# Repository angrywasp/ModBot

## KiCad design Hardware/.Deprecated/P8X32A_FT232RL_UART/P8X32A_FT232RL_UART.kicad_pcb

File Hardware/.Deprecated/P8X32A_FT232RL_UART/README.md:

Not intended for new designs. Outputs are unbuffered. Suitable only for projects that will use USB power through this module

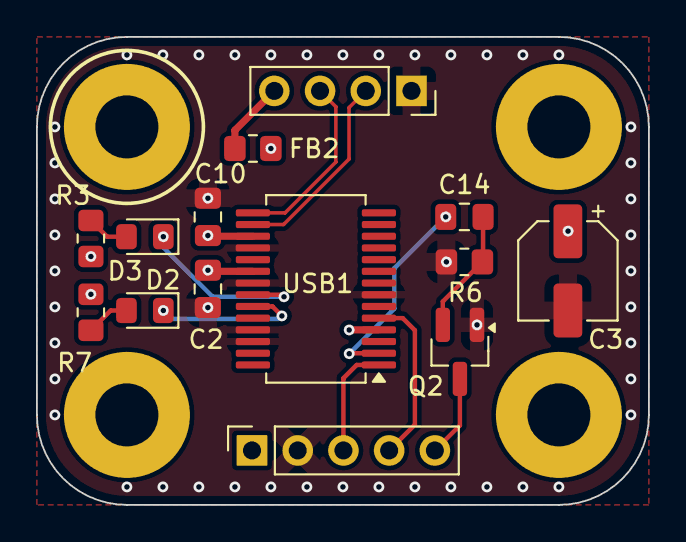
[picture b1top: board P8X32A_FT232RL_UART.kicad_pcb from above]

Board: 4 copper layers, 34.0 x 26.0 mm, 14 parts (0 on the bottom side), 15 nets.

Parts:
C2, C10, C14: 0.1uF; C_0805_2012Metric_Pad1.18x1.45mm_HandSolder
C3: 47uF; CP_Elec_5x5.3
D2: BLUE; LED_0805_2012Metric_Pad1.15x1.40mm_HandSolder
D3: RED; LED_0805_2012Metric_Pad1.15x1.40mm_HandSolder
FB2: 220; R_0805_2012Metric_Pad1.20x1.40mm_HandSolder
J1: Conn_01x05; PinSocket_1x05_P2.54mm_Vertical
J2: Conn_01x04; PinSocket_1x04_P2.54mm_Vertical
Q2: NPN; SOT-23_Handsoldering
R3, R7: 330; R_0805_2012Metric_Pad1.20x1.40mm_HandSolder
R6: 10k; R_0805_2012Metric_Pad1.20x1.40mm_HandSolder
USB1: FT232L; SSOP-28_5.3x10.2mm_P0.65mm

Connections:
+3.3V: C10.2, USB1.4 (VCCIO), USB1.17 (3V3OUT)
+5V: C2.2, C3.1, FB2.2, J1.1, R3.1, R7.2, USB1.20 (VCC)
DTR: C14.1, USB1.2 (DTR)
GND: C2.1, C3.2, C10.1, J1.2, J2.1, Q2.1 (E), R6.2, USB1.7 (GND), USB1.18 (GND), USB1.21 (GND), USB1.25 (AGND), USB1.26 (TEST)
unnamed: D2.2 (A), R7.1
unnamed: D2.1 (K), USB1.23 (CBUS0)
unnamed: D3.2 (A), R3.2
unnamed: D3.1 (K), USB1.22 (CBUS1)
unnamed: FB2.1, J2.4
unnamed: C14.2, Q2.2 (B), R6.1
RESn: J1.5, Q2.3 (C)
RXD: J1.4, USB1.5 (RXD)
TXD: J1.3, USB1.1 (TXD)
USB+: J2.3, USB1.15 (USBD+)
USB-: J2.2, USB1.16 (USBD-)

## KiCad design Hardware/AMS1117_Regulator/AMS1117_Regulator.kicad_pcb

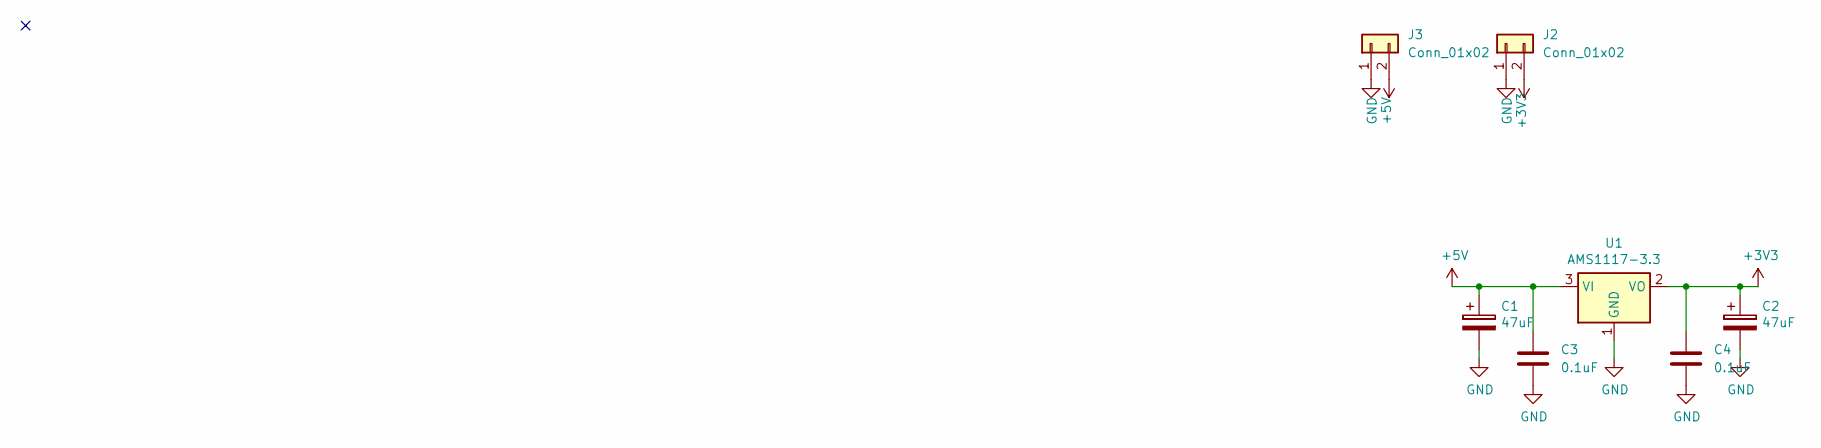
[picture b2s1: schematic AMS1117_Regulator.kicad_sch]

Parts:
C1, C2: 47uF; CP_Elec_5x5.3
C3, C4: 0.1uF; C_0805_2012Metric_Pad1.18x1.45mm_HandSolder
J2, J3: Conn_01x02; PinSocket_1x02_P2.54mm_Vertical
U1: AMS1117-3.3; SOT-223-3_TabPin2

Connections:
+3V3: C2.1, C4.1, J2.2, U1.2 (VO)
+5V: C1.1, C3.1, J3.2, U1.3 (VI)
GND: C1.2, C2.2, C3.2, C4.2, J2.1, J3.1, U1.1 (GND)

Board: 2 copper layers, 7 parts (0 on the bottom side), 3 nets, no tracks yet.

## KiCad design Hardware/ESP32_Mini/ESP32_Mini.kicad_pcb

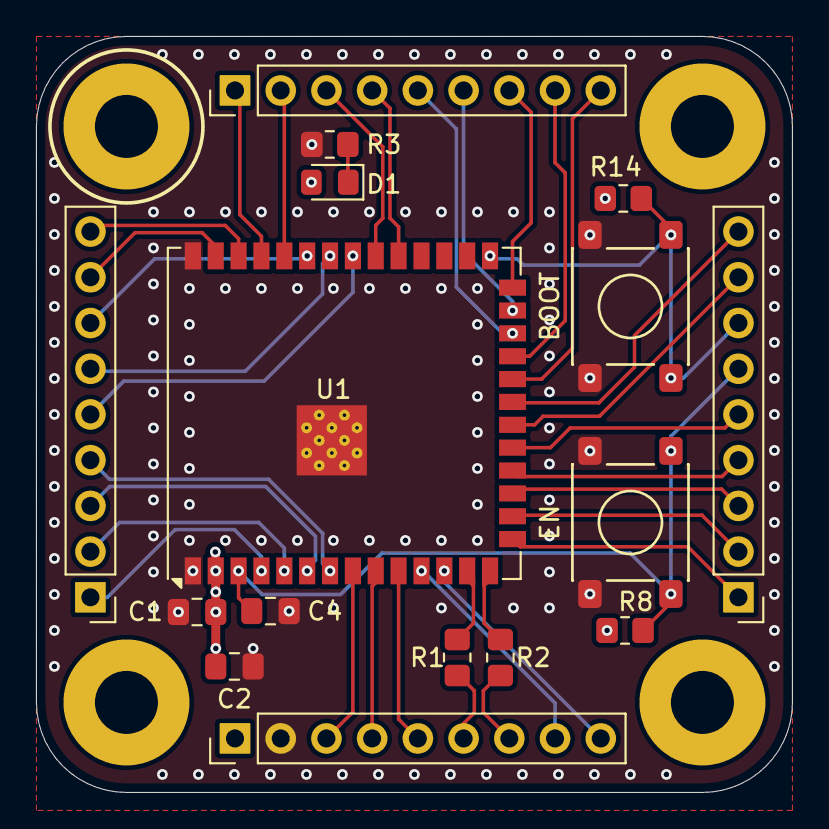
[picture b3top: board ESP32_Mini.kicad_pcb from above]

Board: 4 copper layers, 42.0 x 42.0 mm, 16 parts (0 on the bottom side), 39 nets.

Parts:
C1, C4: 0.1uF; C_0805_2012Metric_Pad1.18x1.45mm_HandSolder
C2: 10uF; C_0805_2012Metric_Pad1.18x1.45mm_HandSolder
D1: LED; LED_0805_2012Metric_Pad1.15x1.40mm_HandSolder
J1, J2: Conn_01x09; PinHeader_1x09_P2.54mm_Vertical
J3, J4: Conn_01x08; PinHeader_1x09_P2.54mm_Vertical
R1, R2: 22; R_0805_2012Metric_Pad1.20x1.40mm_HandSolder
R3, R8, R14: 10k; R_0805_2012Metric_Pad1.20x1.40mm_HandSolder
SW2: BOOT; SW_SPST
SW9: EN; SW_SPST
U1: ESP32-S3-WROOM-1; ESP32-S3-WROOM-1U

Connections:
+3.3V: C1.1, C2.1, D1.2 (A), J3.1, R8.2, R14.2, U1.2 (3V3)
/USB_D+: R2.2, U1.14 (USB_D+)
/USB_D-: R1.2, U1.13 (USB_D-)
D+: J3.7, R2.1
D-: J3.6, R1.1
EN: C4.1, J4.6, R8.1, SW9.2, U1.3 (EN)
GND: C1.2, C2.2, C4.2, J3.2, R3.1, SW2.1, SW9.1, U1.1 (GND), U1.40 (GND), U1.41 (GND)
IO0: J4.7, R14.1, SW2.2, U1.27 (IO0)
IO1: J1.8, U1.39 (IO1)
IO2: J1.9, U1.38 (IO2)
IO3: J4.1, U1.15 (IO3)
IO4: J1.1, U1.4 (IO4)
IO5: J1.2, U1.5 (IO5)
IO6: J1.3, U1.6 (IO6)
IO7: J1.4, U1.7 (IO7)
IO8: J3.9, U1.12 (IO8)
IO9: J4.3, U1.17 (IO9)
IO10: J4.4, U1.18 (IO10)
IO11: J4.5, U1.19 (IO11)
IO12: J4.8, U1.20 (IO12)
IO13: J4.9, U1.21 (IO13)
IO14: J2.9, U1.22 (IO14)
IO15: J3.3, U1.8 (IO15)
IO16: J3.4, U1.9 (IO16)
IO17: J3.5, U1.10 (IO17)
IO18: J3.8, U1.11 (IO18)
IO21: J2.8, U1.23 (IO21)
IO38: J2.4, U1.31 (IO38)
IO39: J2.3, U1.32 (IO39)
IO40: J1.5, U1.33 (IO40)
IO41: J1.6, U1.34 (IO41)
IO42: J1.7, U1.35 (IO42)
IO45: J2.7, U1.26 (IO45)
IO46: J4.2, U1.16 (IO46)
IO47: J2.5, U1.24 (IO47)
IO48: J2.6, U1.25 (IO48)
unnamed: D1.1 (K), R3.2
RXD0: J2.2, U1.36 (RXD0)
TXD0: J2.1, U1.37 (TXD0)

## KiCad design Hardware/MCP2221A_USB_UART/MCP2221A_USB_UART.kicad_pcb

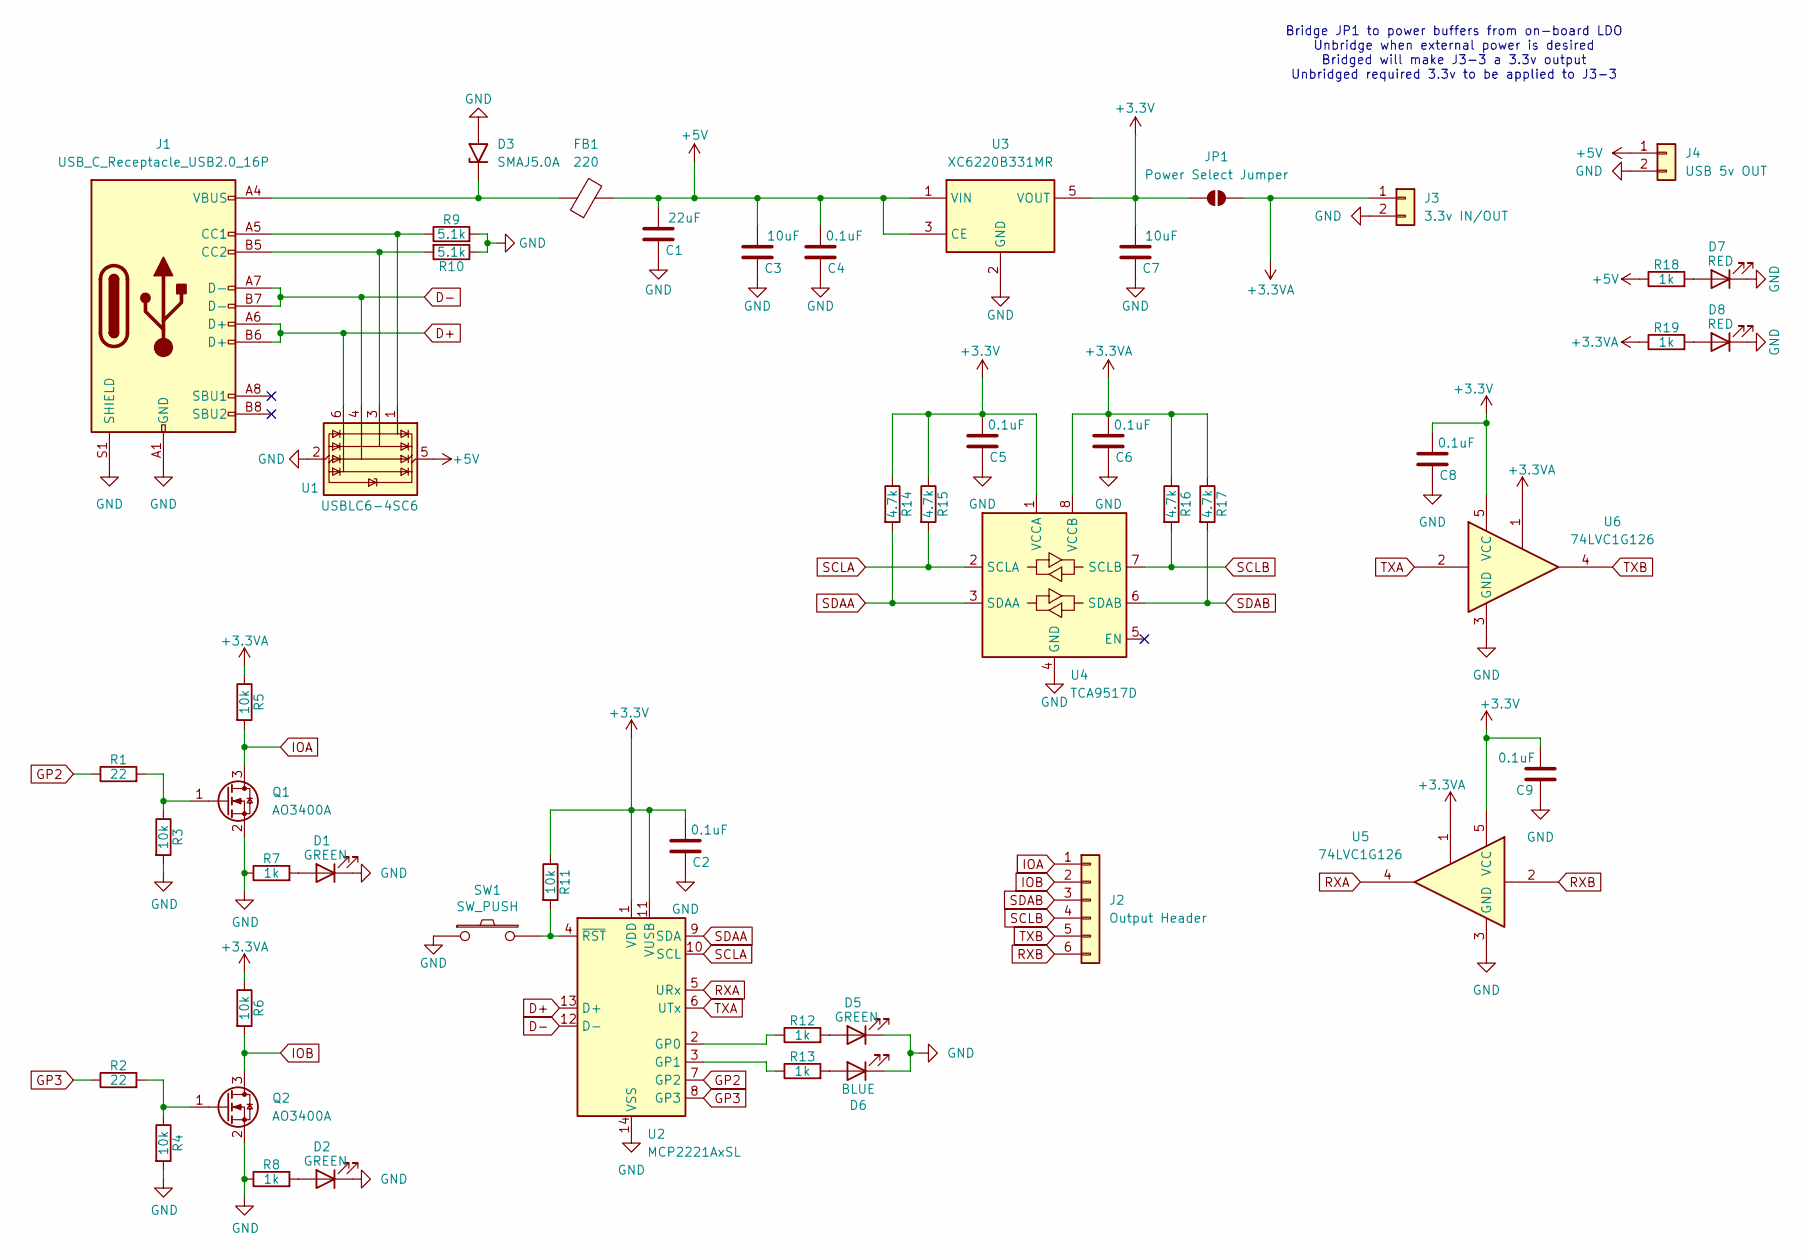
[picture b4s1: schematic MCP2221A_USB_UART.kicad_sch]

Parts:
C1: 22uF; C_0805_2012Metric_Pad1.18x1.45mm_HandSolder
C2, C4, C5, C6, C8, C9: 0.1uF; C_0805_2012Metric_Pad1.18x1.45mm_HandSolder
C3, C7: 10uF; C_0805_2012Metric_Pad1.18x1.45mm_HandSolder
D1, D2, D5: GREEN; LED_0805_2012Metric_Pad1.15x1.40mm_HandSolder
D3: SMAJ5.0A; D_SMA
D6: BLUE; LED_0805_2012Metric_Pad1.15x1.40mm_HandSolder
D7, D8: RED; LED_0805_2012Metric_Pad1.15x1.40mm_HandSolder
FB1: 220; R_0805_2012Metric_Pad1.20x1.40mm_HandSolder
J1: USB_C_Receptacle_USB2.0_16P; USB_C_Receptacle_HCTL_HC-TYPE-C-16P-01A
J2: Output Header; PinHeader_1x06_P2.54mm_Vertical
J3: 3.3v IN/OUT; PinHeader_1x02_P2.54mm_Vertical
J4: USB 5v OUT; PinHeader_1x02_P2.54mm_Vertical
JP1: Power Select Jumper; SolderJumper-2_P1.3mm_Open_RoundedPad1.0x1.5mm
Q1, Q2: AO3400A; SOT-23
R1, R2: 22; R_0805_2012Metric_Pad1.20x1.40mm_HandSolder
R3, R4, R5, R6, R11: 10k; R_0805_2012Metric_Pad1.20x1.40mm_HandSolder
R7, R8, R12, R13, R18, R19: 1k; R_0805_2012Metric_Pad1.20x1.40mm_HandSolder
R9, R10: 5.1k; R_0805_2012Metric_Pad1.20x1.40mm_HandSolder
R14, R15, R16, R17: 4.7k; R_0805_2012Metric_Pad1.20x1.40mm_HandSolder
SW1: SW_PUSH; SW_SPST
U1: USBLC6-4SC6; SOT-23-6
U2: MCP2221AxSL; SOIC-14_3.9x8.7mm_P1.27mm
U3: XC6220B331MR; SOT-23-5
U4: TCA9517D; SOIC-8_3.9x4.9mm_P1.27mm
U5, U6: 74LVC1G126; SOT-23-5

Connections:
+3.3V: C2.2, C5.2, C7.2, C8.2, C9.2, JP1.2 (B), R11.1, R14.1, R15.1, U2.1 (VDD), U2.11 (VUSB), U3.5 (VOUT), U4.1 (VCCA), U5.5 (VCC), U6.5 (VCC)
+3.3VA: C6.2, J3.1, JP1.1 (A), R5.1, R6.1, R16.1, R17.1, R19.1, U4.8 (VCCB), U5.1, U6.1
+5V: C1.2, C3.2, C4.2, FB1.2, J4.1, R18.1, U1.5 (VBUS), U3.1 (VIN), U3.3 (CE)
D+: J1.A6 (D+), J1.B6 (D+), U1.6 (I/O4), U2.13 (D+)
D-: J1.A7 (D-), J1.B7 (D-), U1.4 (I/O3), U2.12 (D-)
GND: C1.1, C2.1, C3.1, C4.1, C5.1, C6.1, C7.1, C8.1, C9.1, D1.1 (K), D2.1 (K), D3.2 (A2), D5.1 (K), D6.1 (K), D7.1 (K), D8.1 (K), J1.A1 (GND), J1.A12 (GND), J1.B1 (GND), J1.B12 (GND), J1.S1 (SHIELD), J3.2, J4.2, Q1.2 (S), Q2.2 (S), R3.2, R4.2, R7.1, R8.1, R9.2, R10.1, SW1.1, U1.2 (GND), U2.14 (VSS), U3.2 (GND), U4.4 (GND), U5.3 (GND), U6.3 (GND)
GP2: R1.1, U2.7 (GP2)
GP3: R2.1, U2.8 (GP3)
IOA: J2.1, Q1.3 (D), R5.2
IOB: J2.2, Q2.3 (D), R6.2
unnamed: D1.2 (A), R7.2
unnamed: D2.2 (A), R8.2
unnamed: D3.1 (A1), FB1.1, J1.A4 (VBUS), J1.A9 (VBUS), J1.B4 (VBUS), J1.B9 (VBUS)
unnamed: D5.2 (A), R12.2
unnamed: D6.2 (A), R13.2
unnamed: D7.2 (A), R18.2
unnamed: D8.2 (A), R19.2
unnamed: J1.A5 (CC1), R9.1, U1.1 (I/O1)
unnamed: J1.B5 (CC2), R10.2, U1.3 (I/O2)
unnamed: Q1.1 (G), R1.2, R3.1
unnamed: Q2.1 (G), R2.2, R4.1
unnamed: R12.1, U2.2 (GP0)
unnamed: R13.1, U2.3 (GP1)
unnamed: R11.2, SW1.2, U2.4 (~RST)
RXA: U2.5 (URx), U5.4
RXB: J2.6, U5.2
SCLA: R15.2, U2.10 (SCL), U4.2 (SCLA)
SCLB: J2.4, R16.2, U4.7 (SCLB)
SDAA: R14.2, U2.9 (SDA), U4.3 (SDAA)
SDAB: J2.3, R17.2, U4.6 (SDAB)
TXA: U2.6 (UTx), U6.2
TXB: J2.5, U6.4

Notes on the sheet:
Bridge JP1 to power buffers from on-board LDO Unbridge when external power is desired Bridged will make J3-3 a 3.3v output Unbridged required 3.3v to be applied to J3-3

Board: 4 copper layers, 50 parts (0 on the bottom side), 32 nets, no tracks yet.

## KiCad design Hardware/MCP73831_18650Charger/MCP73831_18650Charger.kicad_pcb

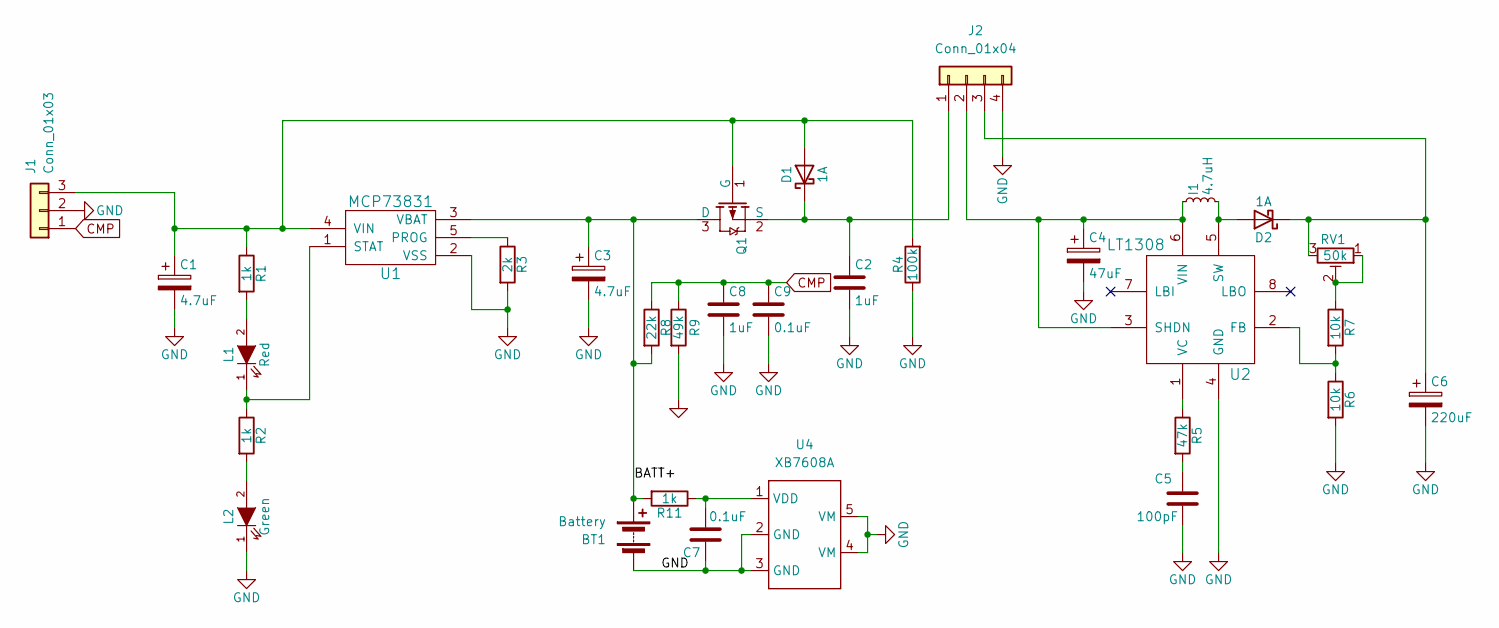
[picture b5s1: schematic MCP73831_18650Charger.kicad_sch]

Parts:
BT1: Battery; Keystone 18650
C1, C3: 4.7uF; CP_Elec_4x5.3
C2, C8: 1uF; C_0805_2012Metric_Pad1.18x1.45mm_HandSolder
C4: 47uF; CP_Elec_5x5.8
C5: 100pF; C_0805_2012Metric_Pad1.18x1.45mm_HandSolder
C6: 220uF; CP_Elec_6.3x7.7
C7, C9: 0.1uF; C_0805_2012Metric_Pad1.18x1.45mm_HandSolder
D1, D2: 1A; D_SMB_Handsoldering
I1: 4.7uH; L_APV_APH0630
J1: Conn_01x03; JST_XH_B3B-XH-A_1x03_P2.50mm_Vertical
J2: Conn_01x04; JST_XH_B4B-XH-A_1x04_P2.50mm_Vertical
L1: Red; LED_0805_2012Metric_Pad1.15x1.40mm_HandSolder
L2: Green; LED_0805_2012Metric_Pad1.15x1.40mm_HandSolder
Q1: PNP; SOT-23_Handsoldering
R1, R2, R11: 1k; R_0805_2012Metric_Pad1.20x1.40mm_HandSolder
R3: 2k; R_0805_2012Metric_Pad1.20x1.40mm_HandSolder
R4: 100k; R_0805_2012Metric_Pad1.20x1.40mm_HandSolder
R5: 47k; R_0805_2012Metric_Pad1.20x1.40mm_HandSolder
R6, R7: 10k; R_0805_2012Metric_Pad1.20x1.40mm_HandSolder
R8: 22k; R_0805_2012Metric_Pad1.20x1.40mm_HandSolder
R9: 49k; R_0805_2012Metric_Pad1.20x1.40mm_HandSolder
RV1: 50k; Potentiometer_Bourns_3224W_Vertical
U1: MCP73831; SOT-23-5_HandSoldering
U2: LT1308; SO-8_3.9x4.9mm_P1.27mm
U4: XB7608A; CPC-5

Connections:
/BATT+: BT1.1 (+), C3.1, Q1.3 (D), R8.2, R11.2, U1.3 (VBAT)
CMP: C8.1, C9.1, J1.1, R8.1, R9.1
GND: BT1.2 (-), C1.2, C2.2, C3.2, C4.2, C5.2, C6.2, C7.1, C8.2, C9.2, J1.2, J2.4, L2.1 (K), R3.2, R4.1, R6.2, R9.2, U1.2 (VSS), U2.4 (GND), U4.2 (GND), U4.3 (GND), U4.4 (VM), U4.5 (VM)
unnamed: C5.1, R5.2
unnamed: C1.1, D1.2 (A), J1.3, Q1.1 (G), R1.1, R4.2, U1.4 (VIN)
unnamed: C2.1, D1.1 (K), J2.1, Q1.2 (S)
unnamed: D2.2 (A), I1.2, U2.5 (SW)
unnamed: C6.1, D2.1 (K), J2.3, RV1.3
unnamed: C4.1, I1.1, J2.2, U2.3 (SHDN), U2.6 (VIN)
unnamed: L1.2 (A), R1.2
unnamed: L1.1 (K), R2.1, U1.1 (STAT)
unnamed: L2.2 (A), R2.2
unnamed: R7.1, RV1.1, RV1.2
unnamed: R3.1, U1.5 (PROG)
unnamed: R6.1, R7.2, U2.2 (FB)
unnamed: R5.1, U2.1 (VC)
unnamed: C7.2, R11.1, U4.1 (VDD)

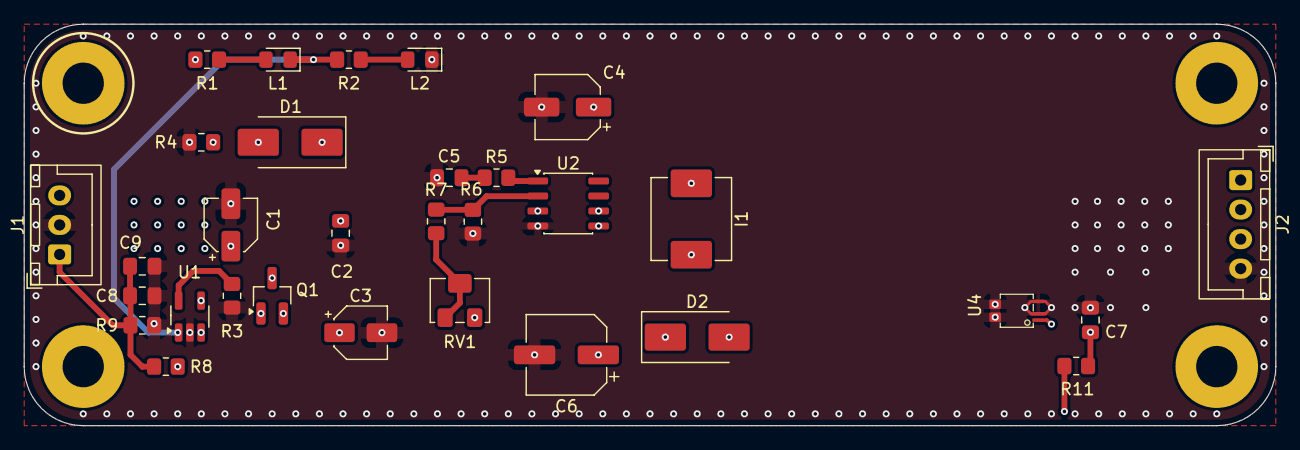
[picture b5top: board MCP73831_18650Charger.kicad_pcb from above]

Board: 4 copper layers, 106.0 x 34.0 mm, 32 parts (1 on the bottom side), 17 nets.

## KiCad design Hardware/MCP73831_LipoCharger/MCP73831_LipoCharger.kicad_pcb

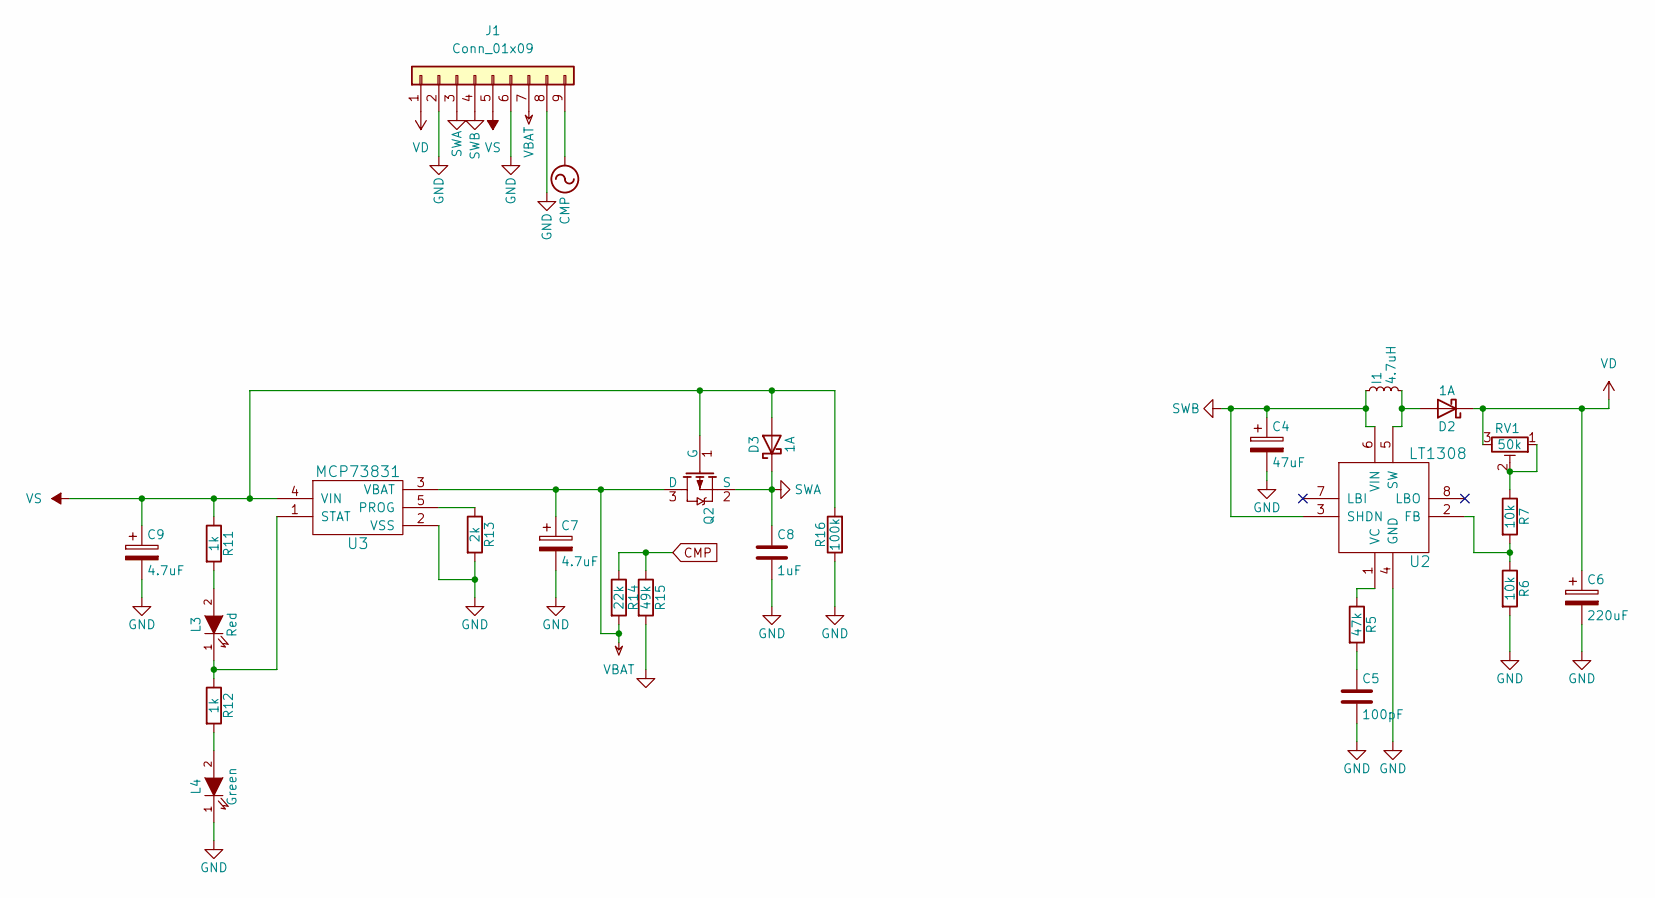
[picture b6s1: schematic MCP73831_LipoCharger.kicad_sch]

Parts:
C4: 47uF; CP_Elec_5x5.8
C5: 100pF; C_0805_2012Metric_Pad1.18x1.45mm_HandSolder
C6: 220uF; CP_Elec_6.3x7.7
C7, C9: 4.7uF; CP_Elec_4x5.3
C8: 1uF; C_0805_2012Metric_Pad1.18x1.45mm_HandSolder
D2, D3: 1A; D_SMB_Handsoldering
I1: 4.7uH; L_APV_APH0630
J1: Conn_01x09; PinSocket_1x09_P2.54mm_Vertical
L3: Red; LED_0805_2012Metric_Pad1.15x1.40mm_HandSolder
L4: Green; LED_0805_2012Metric_Pad1.15x1.40mm_HandSolder
Q2: P-Channel MOSFET; SOT-23_Handsoldering
R5: 47k; R_0805_2012Metric_Pad1.20x1.40mm_HandSolder
R6, R7: 10k; R_0805_2012Metric_Pad1.20x1.40mm_HandSolder
R11, R12: 1k; R_0805_2012Metric_Pad1.20x1.40mm_HandSolder
R13: 2k; R_0805_2012Metric_Pad1.20x1.40mm_HandSolder
R14: 22k; R_0805_2012Metric_Pad1.20x1.40mm_HandSolder
R15: 49k; R_0805_2012Metric_Pad1.20x1.40mm_HandSolder
R16: 100k; R_0805_2012Metric_Pad1.20x1.40mm_HandSolder
RV1: 50k; Potentiometer_Bourns_3224W_Vertical
U2: LT1308; SO-8_3.9x4.9mm_P1.27mm
U3: MCP73831; SOT-23-5_HandSoldering

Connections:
CMP: J1.9, R14.1, R15.1
GND: C4.2, C5.2, C6.2, C7.2, C8.2, C9.2, J1.2, J1.6, J1.8, L4.1 (K), R6.2, R13.2, R15.2, R16.1, U2.4 (GND), U3.2 (VSS)
unnamed: C5.1, R5.2
unnamed: D2.2 (A), I1.2, U2.5 (SW)
unnamed: L3.2 (A), R11.2
unnamed: L3.1 (K), R12.1, U3.1 (STAT)
unnamed: L4.2 (A), R12.2
unnamed: R7.1, RV1.1, RV1.2
unnamed: R6.1, R7.2, U2.2 (FB)
unnamed: R5.1, U2.1 (VC)
unnamed: R13.1, U3.5 (PROG)
SWA: C8.1, D3.1 (K), J1.3, Q2.2 (S)
SWB: C4.1, I1.1, J1.4, U2.3 (SHDN), U2.6 (VIN)
VBAT: C7.1, J1.7, Q2.3 (D), R14.2, U3.3 (VBAT)
VD: C6.1, D2.1 (K), J1.1, RV1.3
VS: C9.1, D3.2 (A), J1.5, Q2.1 (G), R11.1, R16.2, U3.4 (VIN)

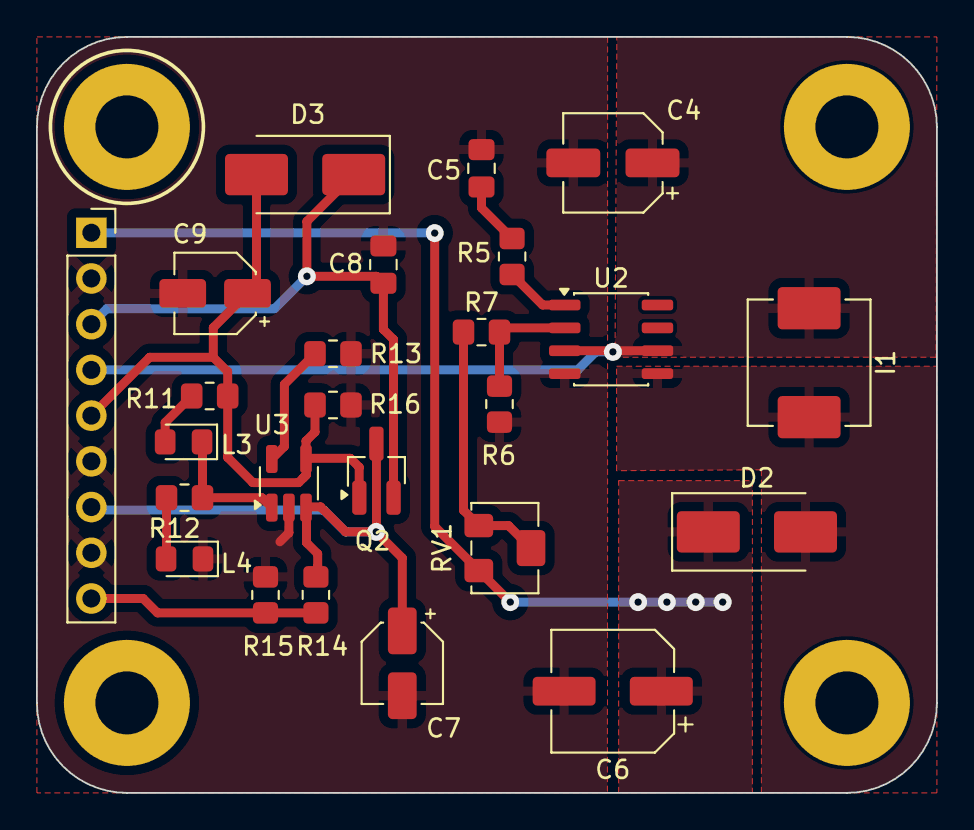
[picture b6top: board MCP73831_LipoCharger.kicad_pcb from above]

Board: 2 copper layers, 50.0 x 42.0 mm, 25 parts (0 on the bottom side), 16 nets.

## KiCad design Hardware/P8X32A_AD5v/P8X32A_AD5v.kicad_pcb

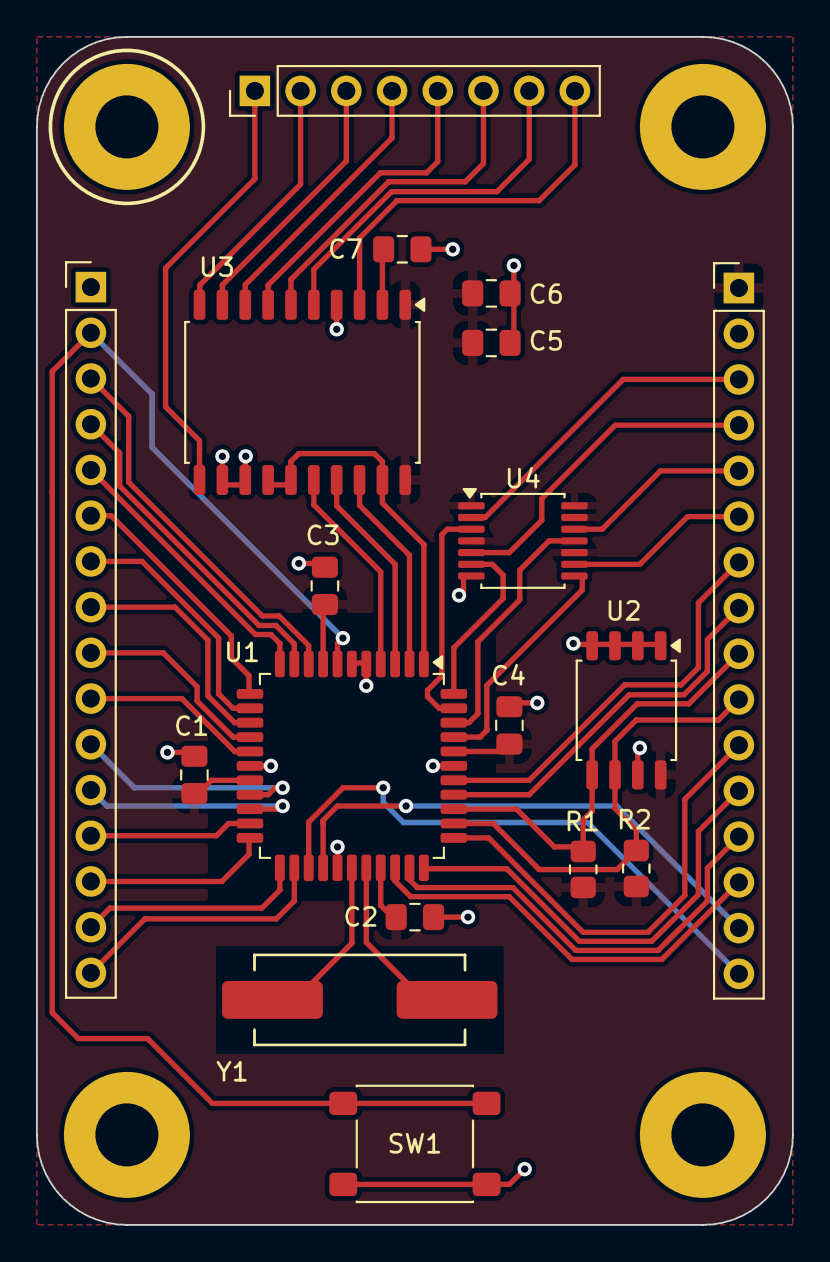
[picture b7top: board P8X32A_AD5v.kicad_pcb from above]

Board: 2 copper layers, 42.0 x 66.0 mm, 18 parts (0 on the bottom side), 50 nets.

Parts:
C1, C2, C3, C4, C6: 0.1uF; C_0805_2012Metric_Pad1.18x1.45mm_HandSolder
C5: 10uF; C_0805_2012Metric_Pad1.18x1.45mm_HandSolder
C7: 10nF; C_0805_2012Metric_Pad1.18x1.45mm_HandSolder
J1, J2: Conn_01x16; PinHeader_1x16_P2.54mm_Vertical
J3: Conn_01x08; PinHeader_1x08_P2.54mm_Vertical
R1, R2: 10k; R_0805_2012Metric_Pad1.20x1.40mm_HandSolder
SW1: SW_PUSH; SW_SPST_PTS645Sx43SMTR92
U1: Propeller; LQFP-44_10x10mm_P0.8mm
U2: 24LC512; SOIC-8_5.3x5.3mm_P1.27mm
U3: AD7812; Infineon_SOIC-20W_7.6x12.8mm_P1.27mm
U4: 74LVC126A; TSSOP-14_4.4x5mm_P0.65mm
Y1: 5Mhz; HC-49

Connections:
1A: J2.3, U4.2 (1A)
1Y: U1.43 (P2), U4.3 (1Y)
2A: J2.4, U4.5 (2A)
2Y: U1.44 (P3), U4.6 (2Y)
3A: J2.6, U4.9 (3A)
3Y: U1.41 (P0), U4.8 (3Y)
4A: J2.5, U4.12 (4A)
4Y: U1.42 (P1), U4.11 (4Y)
+3.3V: C1.2, C2.2, C3.2, C4.2, C5.1, C6.1, J2.1, R1.1, R2.1, U1.8 (VDD), U1.18 (VDD), U1.30 (VDD), U1.40 (VDD), U2.8 (VCC), U3.1 (VREF), U3.20 (VDD), U4.1 (1OE), U4.4 (2OE), U4.10 (3OE), U4.13 (4OE), U4.14 (VCC)
CONVST: U1.1 (P4), U3.14 (TFS), U3.15 (RFS), U3.19 (CONVST)
DIN: U1.3 (P6), U3.17 (DIN)
DOUT: U1.4 (P7), U3.16 (DOUT)
GND: C1.1, C2.1, C3.1, C4.1, C5.2, C6.2, C7.2, J2.2, SW1.2, U1.5 (VSS), U1.6 (BOEn), U1.17 (VSS), U1.27 (VSS), U1.39 (VSS), U2.1 (A0), U2.2 (A1), U2.3 (A2), U2.4 (VSS), U2.7 (WP), U3.4 (AGND), U3.12 (A0), U3.13 (DGND), U4.7 (GND)
unnamed: U1.28 (XI), Y1.2
unnamed: U1.29 (XO), Y1.1
unnamed: C7.1, U3.2 (CREF)
P8: J1.3, U1.9 (P8)
P9: J1.4, U1.10 (P9)
P10: J1.5, U1.11 (P10)
P11: J1.6, U1.12 (P11)
P12: J1.7, U1.13 (P12)
P13: J1.8, U1.14 (P13)
P14: J1.9, U1.15 (P14)
P15: J1.10, U1.16 (P15)
P16: J1.11, U1.19 (P16)
P17: J1.12, U1.20 (P17)
P18: J1.13, U1.21 (P18)
P19: J1.14, U1.22 (P19)
P20: J1.15, U1.23 (P20)
P21: J1.16, U1.24 (P21)
P22: J2.16, U1.25 (P22)
P23: J2.15, U1.26 (P23)
P24: J2.14, U1.31 (P24)
P25: J2.13, U1.32 (P25)
P26: J2.12, U1.33 (P26)
P27: J2.11, U1.34 (P27)
RESn: J1.2, SW1.1, U1.7 (RESn)
RX: J2.7, U1.38 (P31)
SCL: J2.10, R2.2, U1.35 (P28), U2.6 (SCL)
SCLK: U1.2 (P5), U3.18 (SCLK)
SDA: J2.9, R1.2, U1.36 (P29), U2.5 (SDA)
TX: J2.8, U1.37 (P30)
Vin1: J3.8, U3.3 (VIN1)
Vin2: J3.7, U3.5 (VIN2)
Vin3: J3.6, U3.6 (VIN3)
Vin4: J3.5, U3.7 (VIN4)
Vin5: J3.4, U3.8 (VIN5)
Vin6: J3.3, U3.9 (VIN6)
Vin7: J3.2, U3.10 (VIN7)
Vin8: J3.1, U3.11 (VIN8)
